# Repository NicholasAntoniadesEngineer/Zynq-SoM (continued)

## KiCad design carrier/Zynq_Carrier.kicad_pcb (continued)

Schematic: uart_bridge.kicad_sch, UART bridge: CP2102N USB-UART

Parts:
C27001, C27003, C27004: 100n; C_0603_1608Metric; LCSC C14663
C27002: 10u; C_0805_2012Metric; LCSC C15850
R27001: 1k; R_0603_1608Metric; LCSC C21190
R27002: 22k1; R_0603_1608Metric; LCSC C25961
R27003: 47k5; R_0603_1608Metric; LCSC C23061
TP27001: ZYNQ_PS_UART0_TXD; TestPoint_Pad_D1.5mm
TP27002: ZYNQ_PS_UART0_RXD; TestPoint_Pad_D1.5mm
U27001: CP2102N-A02; CP2102N-A02-GQFN24R; LCSC C969151

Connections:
+3V3: C27001.1, C27002.1, C27003.1, C27004.1, R27001.1, U27001.5 (VIO), U27001.6 (VDD), U27001.7 (VREGIN); also elsewhere on the board
/uart_bridge/CP2102N_VBUS_SNS: R27002.2, R27003.1, U27001.8 (VBUS)
GND: C27001.2, C27002.2, C27003.2, C27004.2, R27003.2, U27001.2 (GND), U27001.25 (GND); also elsewhere on the board
unnamed: R27001.2, U27001.9 (RSTb)
USB_UART_DM: U27001.4 (D-); also elsewhere on the board
USB_UART_DP: U27001.3 (D+); also elsewhere on the board
USB_UART_VBUS: R27002.1; also elsewhere on the board
ZYNQ_PS_UART0_CTS_N: U27001.19 (RTS); also elsewhere on the board
ZYNQ_PS_UART0_RTS_N: U27001.18 (CTS); also elsewhere on the board
ZYNQ_PS_UART0_RXD: TP27002.1, U27001.21 (TXD); also elsewhere on the board
ZYNQ_PS_UART0_TXD: TP27001.1, U27001.20 (RXD); also elsewhere on the board

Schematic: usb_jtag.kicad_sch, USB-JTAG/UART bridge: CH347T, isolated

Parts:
C28001: 1u; C_0603_1608Metric; LCSC C15849
C28002: 10u; C_0805_2012Metric; LCSC C15850
C28003, C28004, C28007: 100n; C_0603_1608Metric; LCSC C14663
C28005, C28006: 16p; C_0603_1608Metric; LCSC C327125
R28001, R28002, R28003: 10k; R_0603_1608Metric; LCSC C25804
R28004: 100k; R_0603_1608Metric; LCSC C25803
SW28001: DSHP04TSGER; LCSC C3293144
TP28001: +3V3_DBG; TestPoint_Pad_D1.5mm
TP28002: DBG_UART_TXD; TestPoint_Pad_D1.5mm
TP28003: DBG_UART_RXD; TestPoint_Pad_D1.5mm
U28001: CH347T; LCSC C5122332
U28002: SN74LVC125ADR; LCSC C7661
U28004: AP2112K-3.3TRG1; LCSC C51118
Y28001: 8MHz; 1C208000BC0R; LCSC C57131

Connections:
+3V3_DBG: C28002.1, C28003.1, C28004.1, C28007.1, R28001.1, R28004.1, TP28001.1, U28001.14 (VCC), U28002.14 (VCC), U28004.5 (VOUT)
+5V_DBG: C28001.1, U28004.1 (VIN), U28004.3 (EN); also elsewhere on the board
/usb_jtag/DBG_FT_TCK: U28001.6 (CTS0/GPIO0/SCK/TCK), U28002.2 (1A)
/usb_jtag/DBG_FT_TDI: U28001.8 (TXD0/MOSI/TDI), U28002.5 (2A)
/usb_jtag/DBG_FT_TDO: U28001.7 (RTS0/GPIO1/MISO/TDO), U28002.8 (3Y)
/usb_jtag/DBG_FT_TMS: U28001.5 (DSR0/GPIO2/SCS0/TMS), U28002.12 (4A)
/usb_jtag/DBG_JTAG_OE_N: R28004.2, SW28001.1, U28002.1 (1OE#), U28002.4 (2OE#), U28002.10 (3OE#), U28002.13 (4OE#)
/usb_jtag/DBG_XI: C28005.1, U28001.19 (XI), Y28001.1 (OSC1)
/usb_jtag/DBG_XO: C28006.1, U28001.20 (XO), Y28001.3 (OSC2)
DBG_UART_RXD: TP28003.1, U28001.3 (TXD1); also elsewhere on the board
DBG_UART_TXD: TP28002.1, U28001.4 (RXD1); also elsewhere on the board
DBG_USB_DM: U28001.16 (UD-); also elsewhere on the board
DBG_USB_DP: U28001.17 (UD+); also elsewhere on the board
GND: C28001.2, C28002.2, C28003.2, C28004.2, C28005.2, C28006.2, C28007.2, R28002.2, R28003.2, SW28001.8, U28001.18 (GND), U28002.7 (GND), U28004.2 (GND), Y28001.2 (NC), Y28001.4 (NC); also elsewhere on the board
unnamed: R28001.2, U28001.1 (RST#)
unnamed: R28003.1, U28001.13 (RTS1/GPIO7)
unnamed: R28002.1, U28001.10 (TNOW1/DTR1)
ZYNQ_TCK: U28002.3 (1Y); also elsewhere on the board
ZYNQ_TDI: U28002.6 (2Y); also elsewhere on the board
ZYNQ_TDO: U28002.9 (3A); also elsewhere on the board
ZYNQ_TMS: U28002.11 (4Y); also elsewhere on the board

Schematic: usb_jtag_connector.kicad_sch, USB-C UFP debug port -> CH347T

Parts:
C29001: 10u; C_0805_2012Metric; LCSC C15850
J29001: TYPE-C-31-M-12; LCSC C165948
R29001, R29002: 5.1k; R_0603_1608Metric; LCSC C23186
TP29001: +5V_DBG; TestPoint_Pad_D1.5mm
U29001: USBLC6-2SC6; LCSC C7519

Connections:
+5V_DBG: C29001.1, J29001.A4B9 (VBUS), J29001.B4A9 (VBUS), TP29001.1, U29001.5; also elsewhere on the board
/usb_jtag_connector/DBG_USB_DM_CONN: J29001.A7 (DN1), J29001.B7 (DN2), U29001.3
/usb_jtag_connector/DBG_USB_DP_CONN: J29001.A6 (DP1), J29001.B6 (DP2), U29001.1
CHASSIS_GND: J29001.1 (EH), J29001.2 (EH), J29001.3 (EH), J29001.4 (EH); also elsewhere on the board
DBG_USB_DM: U29001.4; also elsewhere on the board
DBG_USB_DP: U29001.6; also elsewhere on the board
GND: C29001.2, J29001.A1B12 (GND), J29001.B1A12 (GND), R29001.2, R29002.2, U29001.2; also elsewhere on the board
unnamed: J29001.A5 (CC1), R29001.1
unnamed: J29001.B5 (CC2), R29002.1

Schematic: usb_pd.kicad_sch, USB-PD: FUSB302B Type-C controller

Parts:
C30001, C30003: 100n; C_0603_1608Metric; LCSC C14663
C30002: 10u; C_0805_2012Metric; LCSC C15850
C30004, C30005: 200p; C_0603_1608Metric; LCSC C113796
U30001: FUSB302BMPX; WQFN-14-1EP_2.5x2.5mm_P0.5mm_EP1.45x1.45mm; MPN FUSB302BMPX; LCSC C132291

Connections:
+3V3_SC: C30001.1, C30002.1, U30001.3 (VDD), U30001.4 (VDD); also elsewhere on the board
+VBUS_IN: C30003.1, U30001.2 (VBUS); also elsewhere on the board
GND: C30001.2, C30002.2, C30003.2, C30004.2, C30005.2, U30001.8 (GND), U30001.9 (GND), U30001.15 (GND); also elsewhere on the board
SC_INT_N: U30001.5 (INT_N); also elsewhere on the board
STM32_I2C2_SCL: U30001.6 (SCL); also elsewhere on the board
STM32_I2C2_SDA: U30001.7 (SDA); also elsewhere on the board
STM32_USB_CC1: C30004.1, U30001.10 (CC1), U30001.11 (CC1); also elsewhere on the board
STM32_USB_CC2: C30005.1, U30001.1 (CC2), U30001.14 (CC2); also elsewhere on the board

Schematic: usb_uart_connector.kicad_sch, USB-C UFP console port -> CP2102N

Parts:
C31001: 10u; C_0805_2012Metric; LCSC C15850
J31001: TYPE-C-31-M-12; LCSC C165948
R31001, R31002: 5.1k; R_0603_1608Metric; LCSC C23186
U31001: USBLC6-2SC6; LCSC C7519

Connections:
/usb_uart_connector/USB_UART_DM_CONN: J31001.A7 (DN1), J31001.B7 (DN2), U31001.3
/usb_uart_connector/USB_UART_DP_CONN: J31001.A6 (DP1), J31001.B6 (DP2), U31001.1
CHASSIS_GND: J31001.1 (EH), J31001.2 (EH), J31001.3 (EH), J31001.4 (EH); also elsewhere on the board
GND: C31001.2, J31001.A1B12 (GND), J31001.B1A12 (GND), R31001.2, R31002.2, U31001.2; also elsewhere on the board
unnamed: J31001.A5 (CC1), R31001.1
unnamed: J31001.B5 (CC2), R31002.1
USB_UART_DM: U31001.4; also elsewhere on the board
USB_UART_DP: U31001.6; also elsewhere on the board
USB_UART_VBUS: C31001.1, J31001.A4B9 (VBUS), J31001.B4A9 (VBUS), U31001.5; also elsewhere on the board

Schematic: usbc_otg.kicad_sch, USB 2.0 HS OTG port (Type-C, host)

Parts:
C32001: 100n; C_0603_1608Metric; LCSC C14663
C32002: 22u; C_0805_2012Metric; LCSC C45783
C32003: 100u; RVT1C101M0605_100UF_16V; LCSC C970684
J32002: TYPE-C-31-M-12; LCSC C165948
R32001, R32002: 56k; R_0603_1608Metric; LCSC C23206
R32003, R32005: 100k; R_0603_1608Metric; LCSC C25803
R32004: 1k; R_0603_1608Metric; LCSC C21190
TP32001: VBUS_OUT_EN; TestPoint_Pad_D1.5mm
U32001: TPS2051CDBVR; LCSC C129581
U32002: USBLC6-2SC6; LCSC C7519

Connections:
+3V3_SC: R32003.1; also elsewhere on the board
+5V_USB: C32001.1, U32001.5 (IN); also elsewhere on the board
/usbc_otg/USBC_DM_CONN: J32002.A7 (DN1), J32002.B7 (DN2), U32002.3
/usbc_otg/USBC_DP_CONN: J32002.A6 (DP1), J32002.B6 (DP2), U32002.1
CHASSIS_GND: J32002.1 (EH), J32002.2 (EH), J32002.3 (EH), J32002.4 (EH); also elsewhere on the board
GND: C32001.2, C32002.2, C32003.2, J32002.A1B12 (GND), J32002.B1A12 (GND), R32004.2, R32005.2, U32001.2 (GND), U32002.2; also elsewhere on the board
unnamed: J32002.A5 (CC1), R32001.2
unnamed: J32002.B5 (CC2), R32002.2
USBOTG_FLT_N: R32003.2, U32001.3 (FLT#); also elsewhere on the board
USB_D+: U32002.6; also elsewhere on the board
USB_D-: U32002.4; also elsewhere on the board
USB_ID: R32004.1; also elsewhere on the board
USB_VBUS: C32002.1, C32003.1, J32002.A4B9 (VBUS), J32002.B4A9 (VBUS), R32001.1, R32002.1, U32001.1 (OUT), U32002.5; also elsewhere on the board
VBUS_OUT_EN: R32005.1, TP32001.1, U32001.4 (EN(EN#)); also elsewhere on the board

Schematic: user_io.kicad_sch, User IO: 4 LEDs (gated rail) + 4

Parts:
C33001: 100n; C_0603_1608Metric; LCSC C14663
D33001: red; LED_0603_1608Metric; LCSC C2286
D33002: green; LED_0603_1608Metric; LCSC C12624
D33003: blue; LED_0603_1608Metric; LCSC C2288
D33004: white; LED_0603_1608Metric; LCSC C2290
R33001: 1k; R_0603_1608Metric; LCSC C21190
R33002, R33003, R33004: 200R; R_0603_1608Metric; LCSC C8218
R33005, R33006, R33007, R33008: 10k; R_0603_1608Metric; LCSC C25804
SW33001, SW33002, SW33003, SW33004: USER; TS-1187A-B-A-B; LCSC C318884

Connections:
+3V3: R33005.1, R33006.1, R33007.1, R33008.1; also elsewhere on the board
+3V3_USER_LED: C33001.1, D33001.2 (A), D33002.2 (A), D33003.2 (A), D33004.2 (A); also elsewhere on the board
GND: C33001.2, SW33001.3 (C), SW33001.4 (D), SW33002.3 (C), SW33002.4 (D), SW33003.3 (C), SW33003.4 (D), SW33004.3 (C), SW33004.4 (D); also elsewhere on the board
IO_25_13: R33001.2; also elsewhere on the board
IO_L6_P_13: R33002.2; also elsewhere on the board
IO_L15_P_13: R33005.2, SW33001.1 (A), SW33001.2 (B); also elsewhere on the board
IO_L19_P_13: R33006.2, SW33002.1 (A), SW33002.2 (B); also elsewhere on the board
IO_L21_P_13: R33007.2, SW33003.1 (A), SW33003.2 (B); also elsewhere on the board
IO_L22_P_13: R33008.2, SW33004.1 (A), SW33004.2 (B); also elsewhere on the board
IO_L24_N_13: R33004.2; also elsewhere on the board
IO_L24_P_13: R33003.2; also elsewhere on the board
unnamed: D33001.1 (K), R33001.1
unnamed: D33002.1 (K), R33002.1
unnamed: D33003.1 (K), R33003.1
unnamed: D33004.1 (K), R33004.1

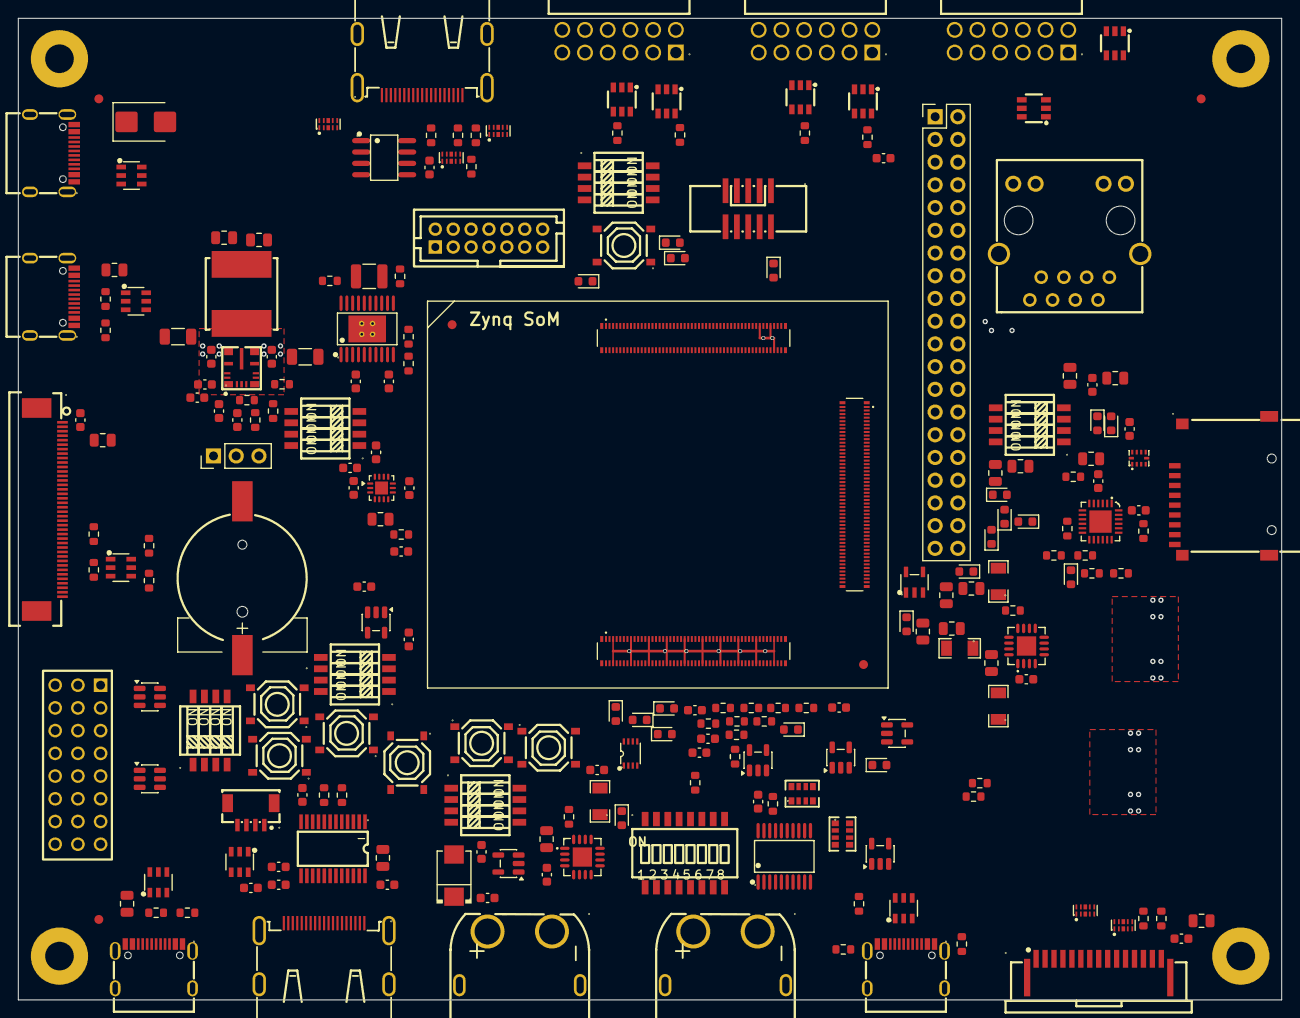
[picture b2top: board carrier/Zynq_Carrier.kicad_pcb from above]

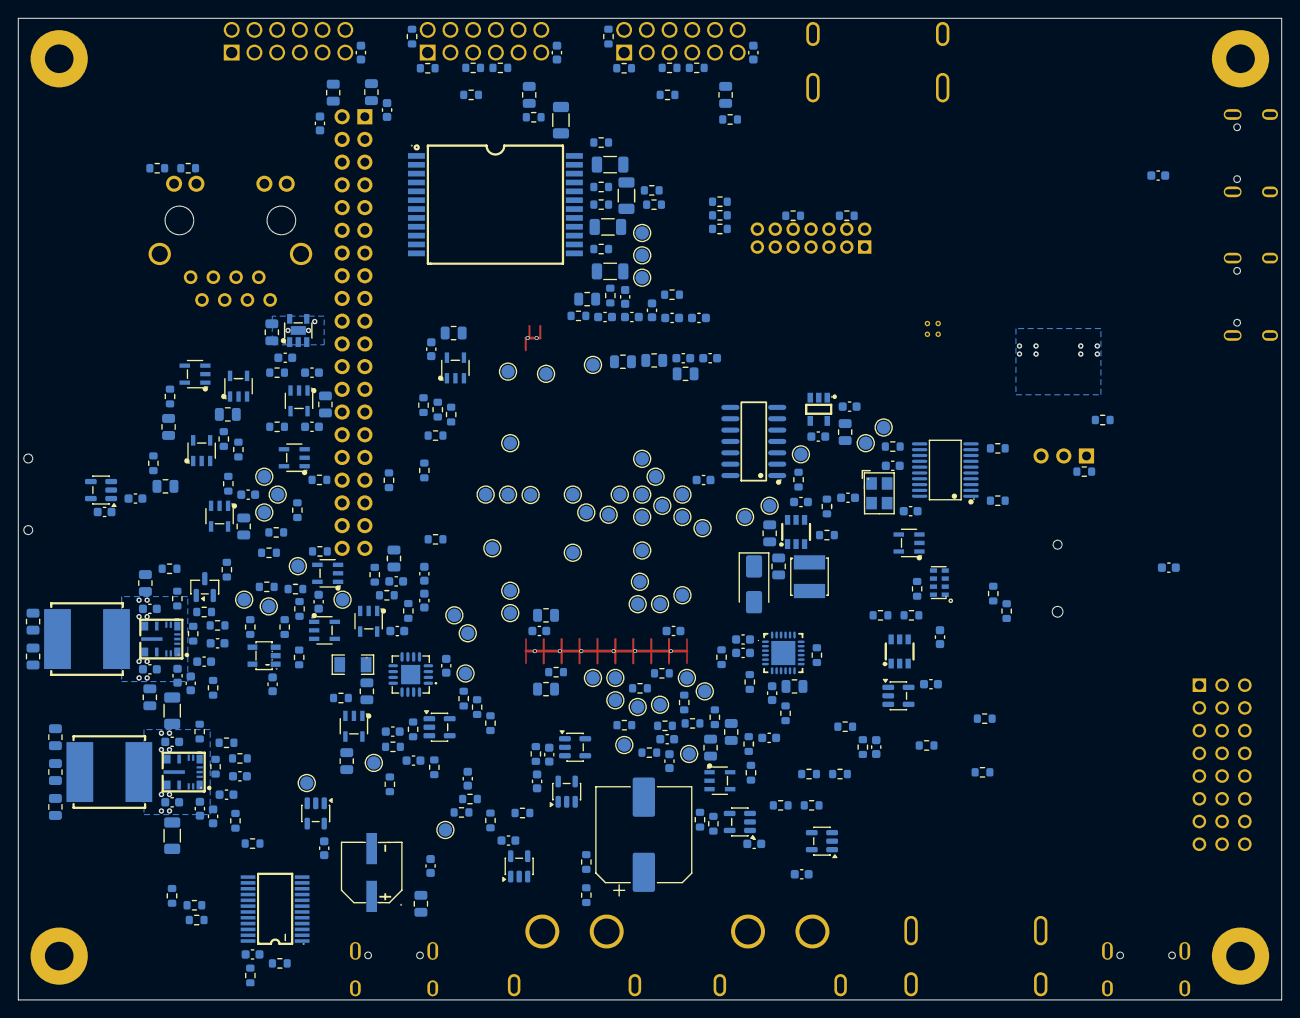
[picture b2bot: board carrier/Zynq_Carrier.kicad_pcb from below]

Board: 6 copper layers, 141.2 x 109.8 mm, 570 parts (342 on the bottom side), 437 nets.

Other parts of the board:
FID1, FID2, FID3, FID4, FID5: Fiducial; Fiducial_1mm_Mask2mm

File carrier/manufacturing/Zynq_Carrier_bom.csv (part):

Comment,Designator,Footprint,JLCPCB Part #
1.5R,R15001,Resistor_SMD:R_0603_1608Metric,C22769
100R,"R8001,R8002,R8003,R9003",Resistor_SMD:R_0603_1608Metric,C22775
100k,"R1002,R1004,R4001,R4002,R4003,R4004,R4005,R4006,R5001,R5002,R5003,R5004,R5005,R5006,R5007,R5008,R5009,R5010,R5011,R5012,R5013,R5014,R5015,R5016,R5017,R5018,R5019,R5020,R5021,R7001,R7002,R7003,R15004,R15005,R16001,R16002,R16003,R16004,R16005,R17003,R17006,R19002,R20008,R28004,R32003,R32005",Resistor_SMD:R_0603_1608Metric,C25803
100n,"C1002,C1004,C2001,C3001,C3002,C3003,C4001,C4002,C4003,C5001,C5002,C5003,C5004,C5005,C5006,C5007,C5008,C5009,C5010,C5011,C6002,C6006,C6008,C6010,C6014,C6020,C7001,C7002,C7003,C8001,C10006,C11002,C11005,C12001,C13001,C14001,C14002,C14003,C15003,C15006,C16001,C16002,C16004,C17001,C17004,C18001,C18003,C19001,C19003,C19004,C20001,C20004,C20007,C20009,C20025,C20029,C21001,C21002,C22014,C22017,C22025,C27001,C27003,C27004,C28003,C28004,C28007,C30001,C30003,C32001,C33001,C35003,C35004,C35005,C35006,C35009,C35010,C35011,C35012,C35015,C35016,C35017,C35018,C36001,C37001,C37002",Capacitor_SMD:C_0603_1608Metric,C14663
100p,C1005,Capacitor_SMD:C_0603_1608Metric,C14858
100u,C32003,RVT1C101M0605_100UF_16V:RVT1C101M0605_100UF_16V,C970684
10R,"R20011,R20013,R22017",Resistor_SMD:R_0603_1608Metric,C22859
10k,"R3001,R3003,R6021,R7006,R7007,R7008,R7009,R9004,R9005,R9006,R12003,R14001,R14002,R15006,R16006,R20002,R20005,R21001,R28001,R28002,R28003,R33005,R33006,R33007,R33008,R36001,R37001",Resistor_SMD:R_0603_1608Metric,C25804
10mR,"RS21001,RS21002,RS21003,RS37001",RLM12FTCMR010:RLM12FTCMR010,C188070
10u,"C1001,C1003,C6001,C6003,C6004,C6005,C6007,C6009,C6011,C6012,C6013,C6015,C6016,C6017,C6018,C6019,C8002,C11001,C11004,C14005,C15001,C15004,C18002,C18004,C19002,C19005,C21003,C27002,C28002,C29001,C30002,C31001,C36002,C36003,C37003",Capacitor_SMD:C_0805_2012Metric,C15850
10u,"C20002,C20003,C22015,C22016",Capacitor_SMD:C_1206_3216Metric,C13585
10u,C17002,Capacitor_SMD:C_1210_3225Metric,C596319
10uH,L15001,SWPA4030S100MT:SWPA4030S100MT,C38117
10uH,"L20001,L20002,L22003",SWPA8040S100MT:SWPA8040S100MT,C37429
13k,"R1001,R6001,R6003,R6007,R6013,R6015,R6017,R19001,R22015,R36002",Resistor_SMD:R_0603_1608Metric,C22797
15k,R12004,Resistor_SMD:R_0603_1608Metric,C22809
16p,"C28005,C28006",Capacitor_SMD:C_0603_1608Metric,C327125
1k,"R3002,R6012,R6018,R6020,R12001,R20003,R20007,R20012,R20015,R22016,R22019,R27001,R32004,R33001",Resistor_SMD:R_0603_1608Metric,C21190
1n,"C10001,C10002,C10003,C10004,C10005",Capacitor_SMD:C_1206_3225Metric,C9196
1u,"C11003,C13002,C14004,C15005,C20012,C20013,C20024,C20028,C20031,C20032,C22022,C22023,C28001",Capacitor_SMD:C_0603_1608Metric,C15849
2.2u,C15002,Capacitor_SMD:C_0805_2012Metric,C125847
200R,"R18001,R18002,R18003,R18004,R18005,R18006,R18007,R18008,R18009,R18010,R18011,R18012,R18013,R18014,R18015,R18016,R33002,R33003,R33004",Resistor_SMD:R_0603_1608Metric,C8218
200p,"C30004,C30005",Capacitor_SMD:C_0603_1608Metric,C113796
20mR,RS21004,RLM12FTCMR020:RLM12FTCMR020,C393094
22R,R15007,Resistor_SMD:R_0603_1608Metric,C23345
22k,"R20010,R20014,R22018",Resistor_SMD:R_0603_1608Metric,C31850
22k1,R27002,Resistor_SMD:R_0603_1608Metric,C25961
22p,"C20023,C20027,C22021",Capacitor_SMD:C_0603_1608Metric,C1653
22u,"C16003,C20005,C20006,C20008,C20010,C20011,C20026,C20030,C22018,C22019,C32002,C35001,C35002,C35007,C35008,C35013,C35014",Capacitor_SMD:C_0805_2012Metric,C45783
23.2k,R20004,Resistor_SMD:R_0603_1608Metric,C23346
24AA025E48T-I/OT,U3001,24AA025E48T-I_OT:24AA025E48T-I_OT,C129895
27k,R12002,Resistor_SMD:R_0603_1608Metric,C22967
330R,"R1003,R6002,R6004,R6006,R6008,R6010,R6014,R6016,R19003,R20006,R20009,R23001,R23002",Resistor_SMD:R_0603_1608Metric,C23138
40.2k,R20001,Resistor_SMD:R_0603_1608Metric,C12447
470uF/35V,C37004,Capacitor_SMD:CP_Elec_10x10.5,C976030
47k5,"R22014,R27003",Resistor_SMD:R_0603_1608Metric,C23061
47n,C17003,Capacitor_SMD:C_0603_1608Metric,C1622
49.9R,"R13001,R13002,R13003,R13004,R13005,R13006,R13007,R13008",Resistor_SMD:R_0603_1608Metric,C114625
4D03WGJ0330T5E,"RN36001,RN36002",4D03WGJ0330T5E:4D03WGJ0330T5E,C25508
4k7,"R1005,R1006,R7004,R7005,R8004,R8005,R9001,R9002,R15002,R15003",Resistor_SMD:R_0603_1608Metric,C23162
5.1k,"R17005,R29001,R29002,R31001,R31002",Resistor_SMD:R_0603_1608Metric,C23186
5.49k,R17004,Resistor_SMD:R_0603_1608Metric,C188263
56k,"R32001,R32002",Resistor_SMD:R_0603_1608Metric,C23206
6.8k,"R6005,R6009,R6011,R6019",Resistor_SMD:R_0603_1608Metric,C23212
75R,"R10001,R10002,R10003,R10004",Resistor_SMD:R_0603_1608Metric,C4275
878311420,J9001,878311420:878311420,C240854
8MHz,Y28001,1C208000BC0R:1C208000BC0R,C57131
AFC07-S40FCA-00,J15001,AFC07-S40FCA-00:AFC07-S40FCA-00,C262572
AO3400A,Q20001,Package_TO_SOT_SMD:SOT-23,C20917
AP2112K-1.8,U20003,Package_TO_SOT_SMD:SOT-23-5,C176944
AP2112K-3.3TRG1,U28004,AP2112K-3.3TRG1:AP2112K-3.3TRG1,C51118
CH347T,U28001,CH347T:CH347T,C5122332
CP2102N-A02,U27001,CP2102N-A02-GQFN24R:CP2102N-A02-GQFN24R,C969151
DF40C-100DP-0.4V(51),"J24001,J25002,J26003",Mylibrary:HRS_DF40C-100DP-0.4V_51_,C531031
DIP-4,"SW1001,SW7001,SW7006,SW9001,SW19001,SW28001",DSHP04TSGER:DSHP04TSGER,C3293144
DS1024-2x6R2,"J18001,J18002,J19001",DS1024-2x6R2:DS1024-2x6R2,C49284652
DSHP08TSGER,SW7002,DSHP08TSGER:DSHP08TSGER,C3293147
FUSB302BMPX,U30001,Package_DFN_QFN:WQFN-14-1EP_2.5x2.5mm_P0.5mm_EP1.45x1.45mm,C132291
HDMI-019S,"J12001,J14001",HDMI-019S:HDMI-019S,C111617
HX PZ2.54-3x8P ZZ,J36001,HX_PZ2.54-3x8P_ZZ:HX_PZ2.54-3x8P_ZZ,C32713295
HX5008NLT,T10001,HX5008NLT:HX5008NLT,C962544
HX_JN1.27-2x5,J9002,HX_JN1.27-2x5_TP_H4.9:HX_JN1.27-2x5_TP_H4.9,C42372555
Header_1x03_2.54mm,J3001,Connector_PinHeader_2.54mm:PinHeader_1x03_P2.54mm_Vertical,C49257
Header_2x20_2.54mm,J11001,Connector_PinHeader_2.54mm:PinHeader_2x20_P2.54mm_Vertical,C50980
INA3221AIRGVR,"U21001,U21002,U37002",INA3221AIRGVR:INA3221AIRGVR,C181255
KH-5224-8P8C-D,J23001,KH-5224-8P8C-D:KH-5224-8P8C-D,C2828085
KH-CR1220-2,BT3001,KH-CR1220-2:KH-CR1220-2,C5365933
LM61460AANRJRR,"U20001,U20002,U22004",LM61460AANRJRR:LM61460AANRJRR,C2864505
M24C02-WMN6TP,U12001,M24C02-WMN6TP:M24C02-WMN6TP,C7562
PCA9306DCUR,U1002,PCA9306DCUR:PCA9306DCUR,C33196
RESET,"SW7003,SW7004,SW9002,SW33001,SW33002,SW33003,SW33004",TS-1187A-B-A-B:TS-1187A-B-A-B,C318884
RV-3028-C7-32.768kHz-1ppm-TA-QC,U3002,RV-3028-C7-32.768kHz-1ppm-TA-QC:RV-3028-C7-32.768kHz-1ppm-TA-QC,C3019759
SFW15R-1STE1LF,J8001,SFW15R-1STE1LF:SFW15R-1STE1LF,C3168538
SMBJ22A,D17001,Diode_SMD:D_SMB,C10214
SMBJ28A,D37001,SMBJ28A:SMBJ28A,C178227
SN74HCT245PWR,U36001,SN74HCT245PWR:SN74HCT245PWR,C6779
SN74LVC125ADR,U28002,SN74LVC125ADR:SN74LVC125ADR,C7661
SN74LVC1G08,"U4001,U4002,U4003,U5001,U5002,U5003,U5004,U5005,U5006,U5007,U5008,U5009,U5010,U5011",Package_TO_SOT_SMD:SOT-23-5,C7666
SRV05-4,"D36001,D36002",Package_TO_SOT_SMD:SOT-23-6,C2836319
SS34,D15001,Diode_SMD:D_SMA,C8678
SY6280AAC,"U1001,U6001,U6002,U6003,U6004,U6005,U6006,U6007,U6008,U6009,U6010,U19001,U36003",SY6280AAC:SY6280AAC,C55136
SY7201ABC,U15001,SY7201ABC:SY7201ABC,C82173
TCA9535PWR,U7001,TCA9535PWR:TCA9535PWR,C130204
TF-01A,J16001,TF-01A:TF-01A,C91145
TLV75725PDYDR,U11001,TLV75725PDYDR:TLV75725PDYDR,C35209004
TPD12S016PWR,U14001,TPD12S016PWR:TPD12S016PWR,C201665
TPD4E02B04DQAR,"U8001,U8002,U12002,U12003",TPD4E02B04DQAR:TPD4E02B04DQAR,C106794
TPD4E05U06DQAR,U12004,TPD4E05U06DQAR:TPD4E05U06DQAR,C138714
TPD4E1U06,"U18001,U18002,U18003,U18004,U19002,U19003",TPD4E1U06DBVR:TPD4E1U06DBVR,C124691
TPD6E001RSER,U16002,TPD6E001RSER:TPD6E001RSER,C1973318
TPS2051CDBVR,U32001,TPS2051CDBVR:TPS2051CDBVR,C129581
TPS26631PWPR,U17001,TPS26631PWPR:TPS26631PWPR,C2866319
TPS3823-33DBVR,U3003,TPS3823-33DBVR:TPS3823-33DBVR,C7719
TXS02612RTWR,U16001,TXS02612RTWR:TXS02612RTWR,C140276
TYPE-C-31-M-12,"J17001,J29001,J31001,J32002",TYPE-C-31-M-12:TYPE-C-31-M-12,C165948
USBLC6-2SC6,"U2001,U15002,U17002,U29001,U31001,U32002",USBLC6-2SC6:USBLC6-2SC6,C7519
XT60PW-M,"J37002,J37003",XT60PW-M:XT60PW-M,C98732
ZX-SH1.0-4PLT,J2001,ZX-SH1.0-4PLT:ZX-SH1.0-4PLT,C7430453
blue,D33003,LED_SMD:LED_0603_1608Metric,C2288
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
